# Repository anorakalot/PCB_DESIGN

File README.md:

# PCB_DESIGN
PCB_DESIGN REPOSITORY

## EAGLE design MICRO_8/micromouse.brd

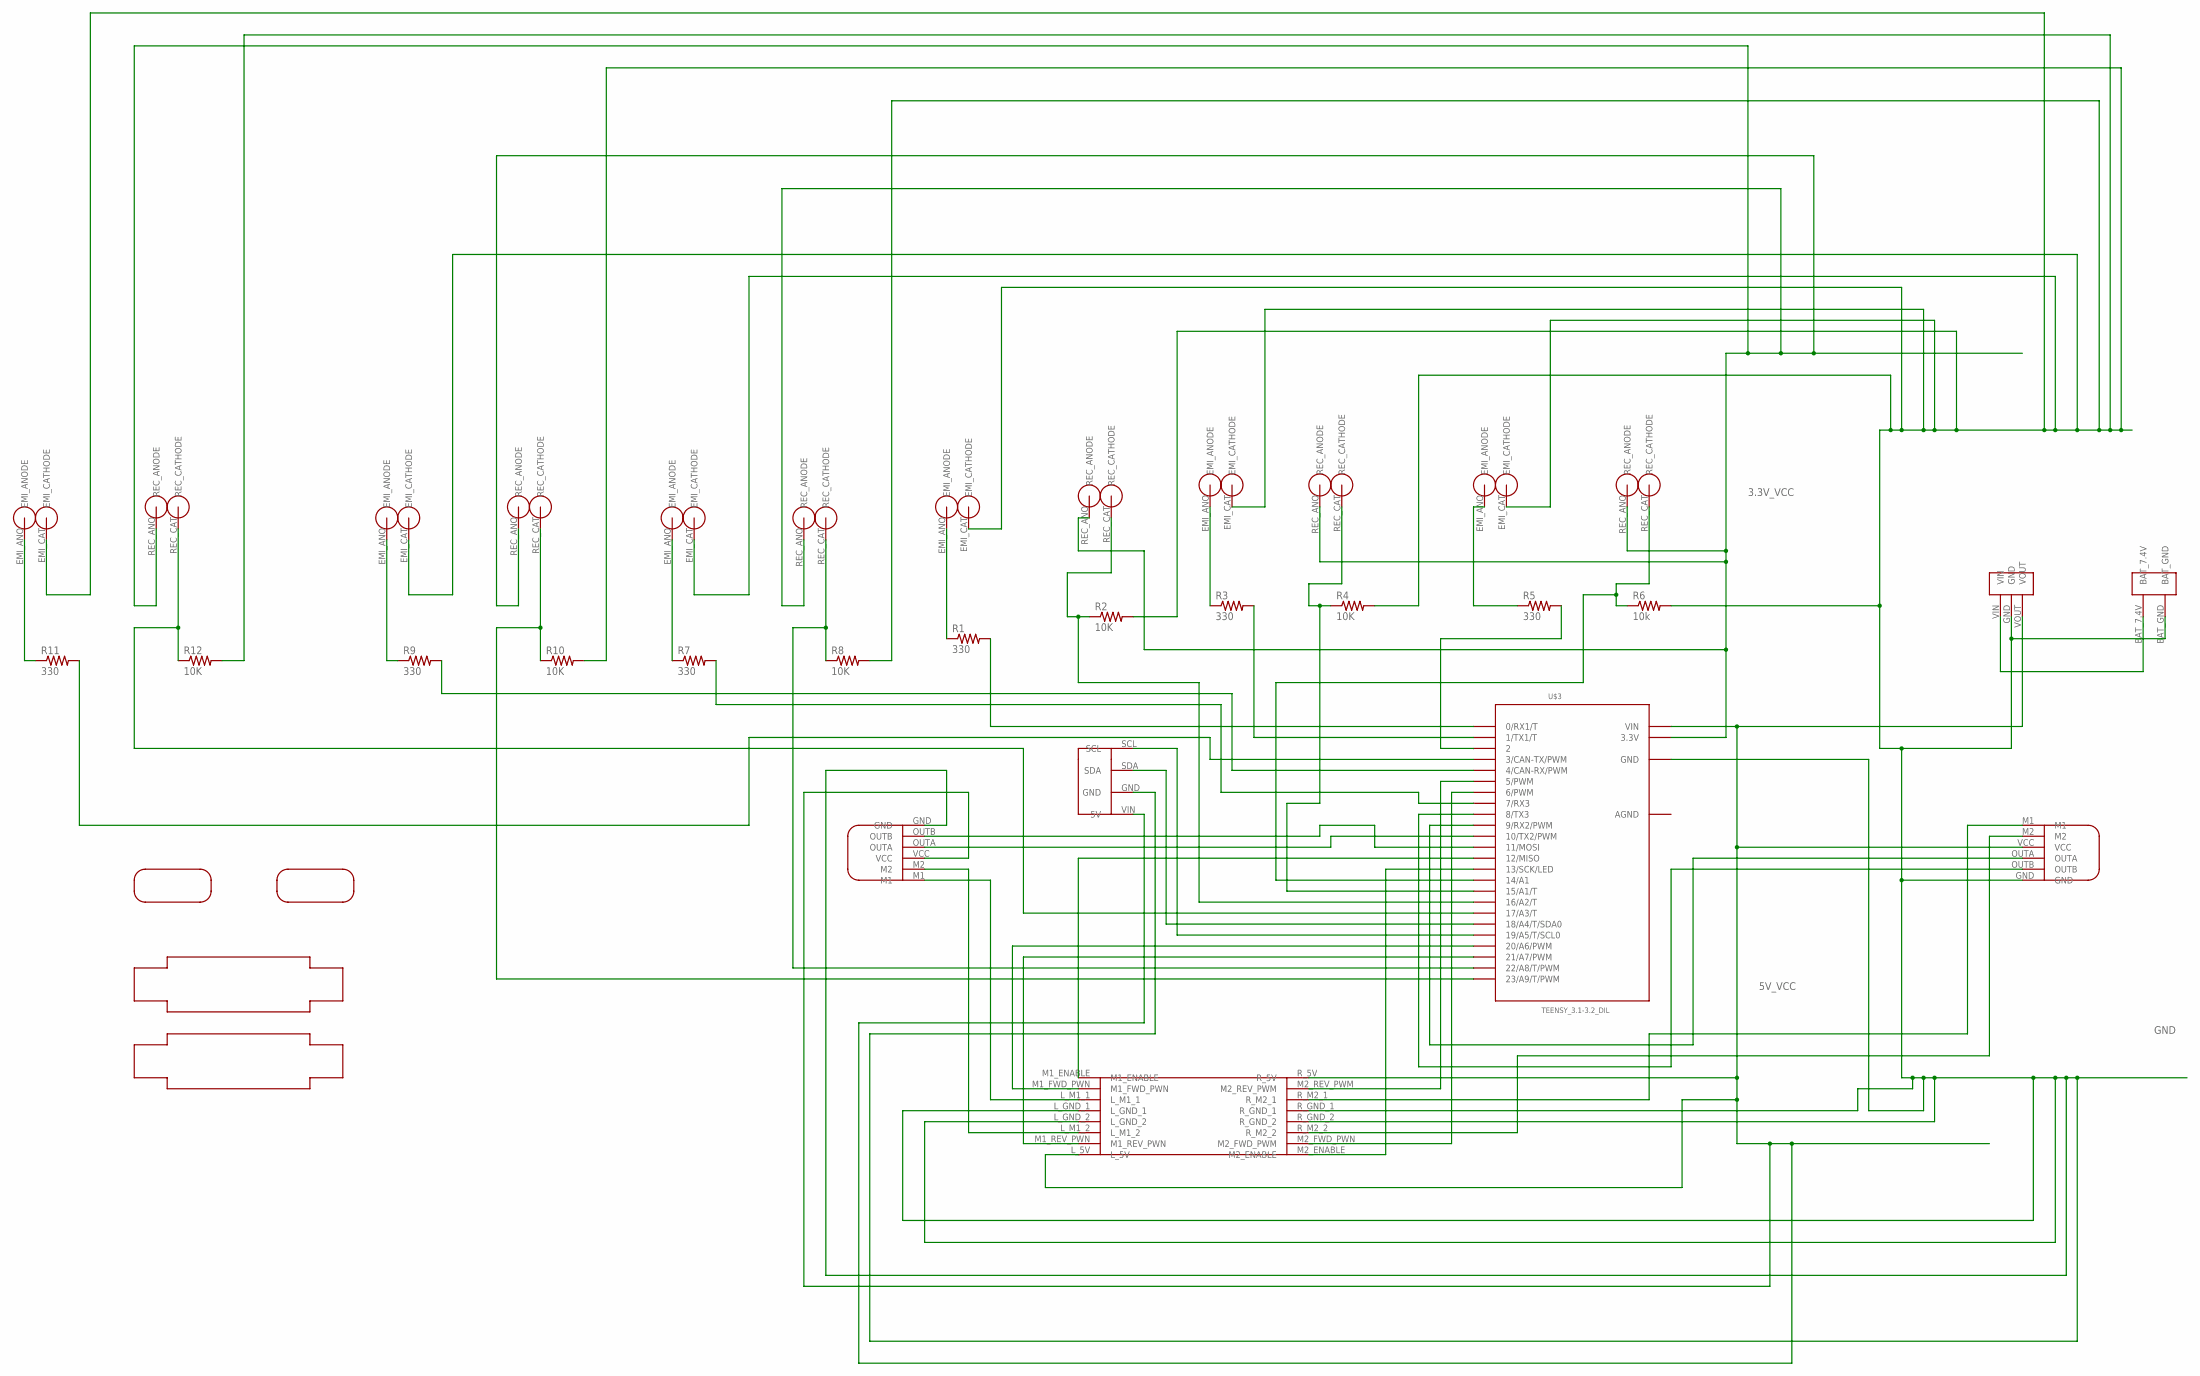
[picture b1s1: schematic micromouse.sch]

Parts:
R1, R3, R5, R7, R9, R11: 330; 0207/10
R2, R4, R8, R10, R12: 10K; 0207/10
R6: 10k; 0207/10
U$1, U$2: MOTOR_ENCODER
U$3: TEENSY_3.1-3.2_DIL; TEENSY_3.0-3.2&LC_DIL
U$4: MOTOR_DRIVER
U$5, U$8, U$12, U$15, U$17, U$23: IR_RECIEVER
U$6, U$7, U$9, U$14, U$16, U$22: IR_EMITTER
U$10: VOLTAGE_REGULATOR
U$11: BATTERY_INPUT
U$13: IMU
U$18, U$19: MOTOR_BRACKET
U$20, U$21: BALL_CASTER

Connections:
3.3V_VCC: U$3.3.3V, U$5.REC_ANO (REC_ANODE), U$8.REC_ANO (REC_ANODE), U$12.REC_ANO (REC_ANODE), U$15.REC_ANO (REC_ANODE), U$17.REC_ANO (REC_ANODE), U$23.REC_ANO (REC_ANODE)
5V_VCC: U$1.VCC, U$2.VCC, U$3.VIN, U$4.L_5V, U$4.R_5V, U$10.VOUT, U$13.VIN (5V)
AGND: U$3.AGND
GND: R2.2, R4.2, R6.2, R8.2, R10.2, R12.2, U$1.GND, U$2.GND, U$3.GND, U$4.L_GND_1, U$4.L_GND_2, U$4.R_GND_1, U$4.R_GND_2, U$6.EMI_CAT (EMI_CATHODE), U$7.EMI_CAT (EMI_CATHODE), U$9.EMI_CAT (EMI_CATHODE), U$10.GND, U$11.BAT_GND, U$13.GND, U$14.EMI_CAT (EMI_CATHODE), U$16.EMI_CAT (EMI_CATHODE), U$22.EMI_CAT (EMI_CATHODE)
M1_FWD_PWM: U$3.20/A6 (20/A6/PWM), U$4.M1_FWD_PWN
M1_L: U$1.M1, U$4.L_M1_1
M1_R: U$2.M1, U$4.R_M2_1
M1_REV_PWM: U$3.21/A7 (21/A7/PWM), U$4.M1_REV_PWN
M2_ENABLE: U$3.13 (13/SCK/LED), U$4.M2_ENABLE
M2_FWD_PWM: U$3.6 (6/PWM), U$4.M2_FWD_PWN (M2_FWD_PWM)
M2_L: U$1.M2, U$4.L_M1_2
M2_R: U$2.M2, U$4.R_M2_2
unnamed: U$10.VIN, U$11.BAT_7.4V
unnamed: U$3.19/A5 (19/A5/T/SCL0), U$13.SCL
unnamed: U$3.18/A4 (18/A4/T/SDA0), U$13.SDA
unnamed: U$3.12 (12/MISO), U$4.M1_ENABLE
unnamed: U$3.5 (5/PWM), U$4.M2_REV_PWM
unnamed: R7.2, U$3.3 (3/CAN-TX/PWM)
unnamed: R7.1, U$14.EMI_ANO (EMI_ANODE)
unnamed: R8.1, U$3.22/A8 (22/A8/T/PWM), U$15.REC_CAT (REC_CATHODE)
unnamed: R9.2, U$3.4 (4/CAN-RX/PWM)
unnamed: R9.1, U$16.EMI_ANO (EMI_ANODE)
unnamed: R11.2, U$3.7 (7/RX3)
unnamed: R10.1, U$3.23/A9 (23/A9/T/PWM), U$17.REC_CAT (REC_CATHODE)
unnamed: R11.1, U$22.EMI_ANO (EMI_ANODE)
unnamed: R12.1, U$3.17/A3 (17/A3/T), U$23.REC_CAT (REC_CATHODE)
unnamed: R1.2, U$3.0 (0/RX1/T)
unnamed: R1.1, U$9.EMI_ANO (EMI_ANODE)
unnamed: R6.1, U$3.14/A0 (14/A1), U$8.REC_CAT (REC_CATHODE)
unnamed: R3.2, U$3.1 (1/TX1/T)
unnamed: R3.1, U$6.EMI_ANO (EMI_ANODE)
unnamed: R4.1, U$3.15/A1 (15/A1/T), U$12.REC_CAT (REC_CATHODE)
unnamed: R5.2, U$3.2
unnamed: R5.1, U$7.EMI_ANO (EMI_ANODE)
unnamed: R2.1, U$3.16/A2 (16/A2/T), U$5.REC_CAT (REC_CATHODE)
OUTA_L: U$1.OUTA, U$3.10 (10/TX2/PWM)
OUTA_R: U$2.OUTA, U$3.9 (9/RX2/PWM)
OUTB_L: U$1.OUTB, U$3.11 (11/MOSI)
OUTB_R: U$2.OUTB, U$3.8 (8/TX3)

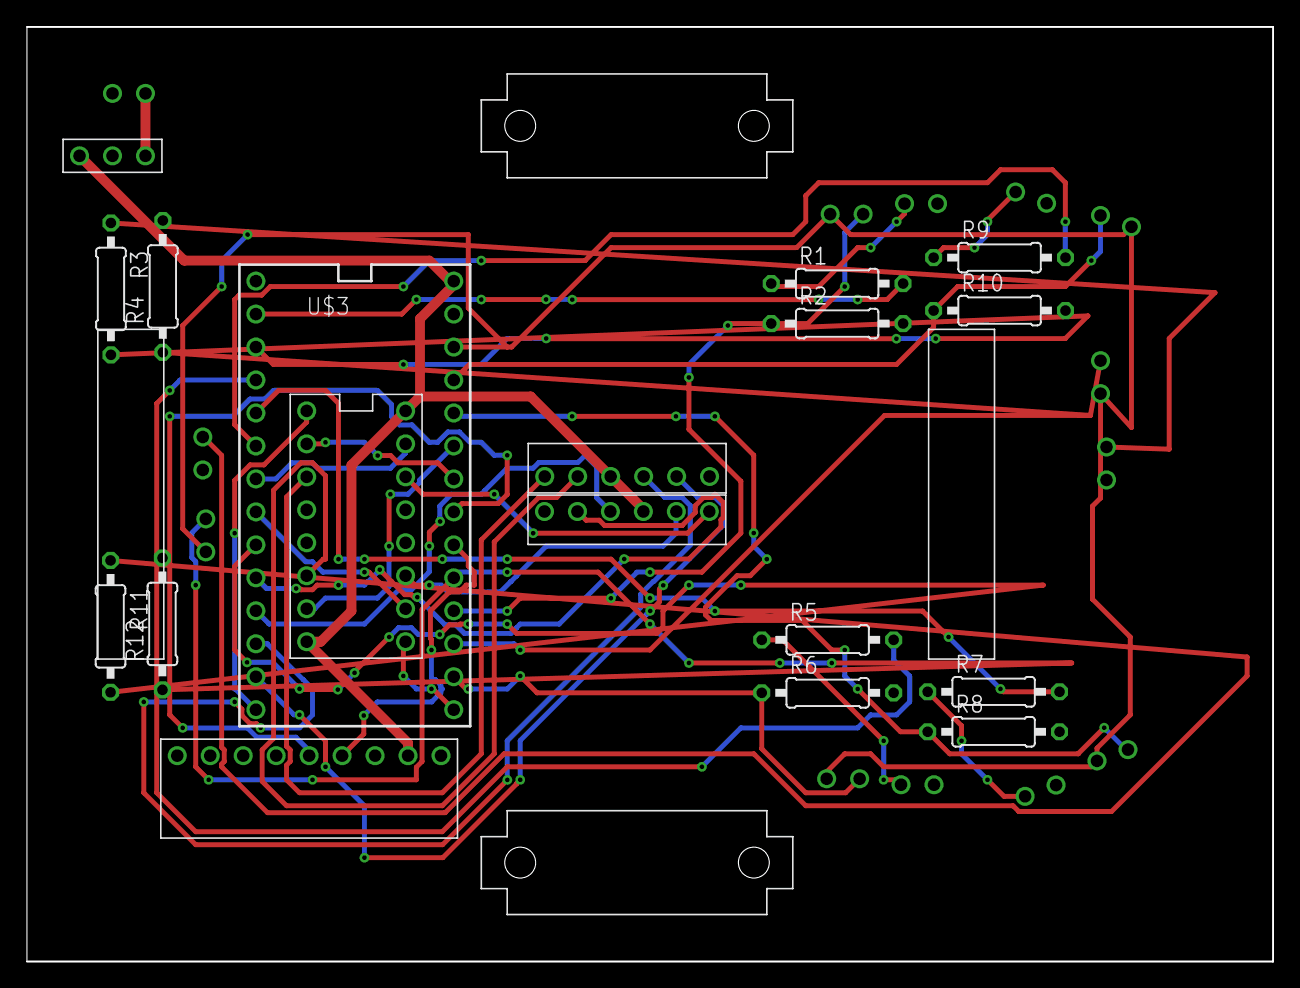
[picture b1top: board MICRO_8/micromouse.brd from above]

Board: 2 copper layers, 96.0 x 72.0 mm, 35 parts (0 on the bottom side), 38 nets.

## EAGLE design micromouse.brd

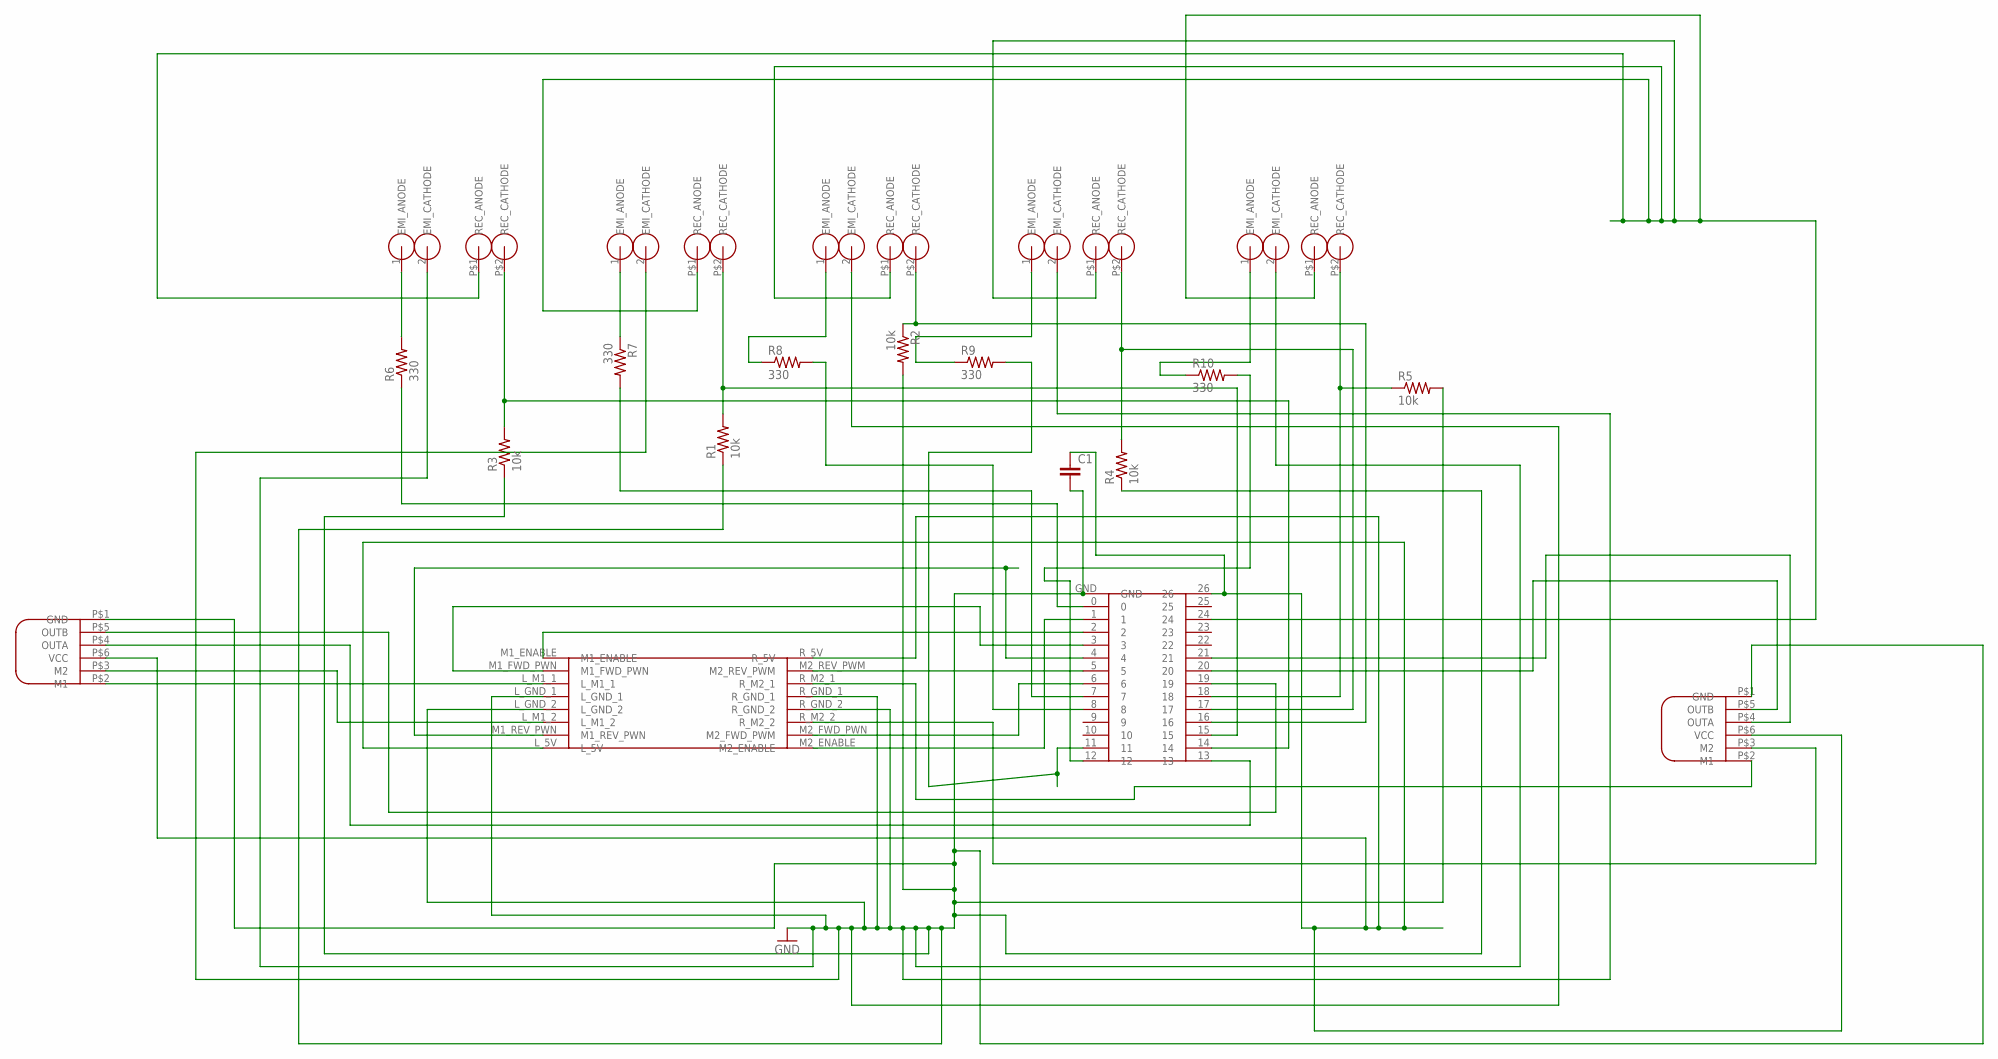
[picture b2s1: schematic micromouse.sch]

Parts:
C1: C2,5-3; C2.5-3
R1, R2, R3, R4, R5: 10k; 0204/5
R6, R7, R8, R9, R10: 330; 0204/5
U$1: TEENSY3.2
U$2: MOTOR_DRIVER
U$3, U$4, U$5, U$6, U$7: IR_RECIEVER
U$8, U$9, U$10, U$11, U$12: IR_EMITTER
U$13, U$14: MOTOR_ENCODER

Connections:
GND: C1.2, R1.1, R2.2, R3.1, R4.1, R5.2, U$1.GND, U$2.L_GND_1, U$2.L_GND_2, U$2.R_GND_1, U$2.R_GND_2, U$8.2 (EMI_CATHODE), U$9.2 (EMI_CATHODE), U$10.2 (EMI_CATHODE), U$11.2 (EMI_CATHODE), U$12.2 (EMI_CATHODE), U$13.P$1 (GND), U$14.P$1 (GND)
unnamed: U$1.2, U$2.M1_ENABLE
unnamed: U$1.3, U$2.M1_FWD_PWN
unnamed: U$2.L_M1_2, U$13.P$3 (M2)
unnamed: U$1.1, U$2.M2_ENABLE
unnamed: U$1.5, U$2.M2_REV_PWM
unnamed: U$2.R_M2_2, U$14.P$3 (M2)
unnamed: U$1.6, U$2.M2_FWD_PWN (M2_FWD_PWM)
unnamed: U$1.4, U$2.M1_REV_PWN
unnamed: R6.2, U$8.1 (EMI_ANODE)
unnamed: R6.1, U$1.0
unnamed: R7.1, U$9.1 (EMI_ANODE)
unnamed: R7.2, U$1.7
unnamed: R8.1, U$10.1 (EMI_ANODE)
unnamed: R8.2, U$1.8
unnamed: R9.1, U$11.1 (EMI_ANODE)
unnamed: R9.2, U$1.11
unnamed: R10.1, U$12.1 (EMI_ANODE)
unnamed: R10.2, U$1.12
unnamed: R1.2, U$1.15, U$4.P$2 (REC_CATHODE)
unnamed: R2.1, U$1.16, U$5.P$2 (REC_CATHODE)
unnamed: R4.2, U$1.17, U$6.P$2 (REC_CATHODE)
unnamed: R5.1, U$1.18, U$7.P$2 (REC_CATHODE)
unnamed: R3.2, U$1.14, U$3.P$2 (REC_CATHODE)
unnamed: U$2.L_M1_1, U$13.P$2 (M1)
unnamed: U$1.20, U$14.P$5 (OUTB)
unnamed: U$1.13, U$13.P$4 (OUTA)
unnamed: U$1.21, U$14.P$4 (OUTA)
unnamed: U$1.19, U$13.P$5 (OUTB)
unnamed: C1.1, U$1.26, U$2.L_5V, U$2.R_5V, U$13.P$6 (VCC), U$14.P$6 (VCC)
unnamed: U$2.R_M2_1, U$14.P$2 (M1)
unnamed: U$1.24, U$3.P$1 (REC_ANODE), U$4.P$1 (REC_ANODE), U$5.P$1 (REC_ANODE), U$6.P$1 (REC_ANODE), U$7.P$1 (REC_ANODE)

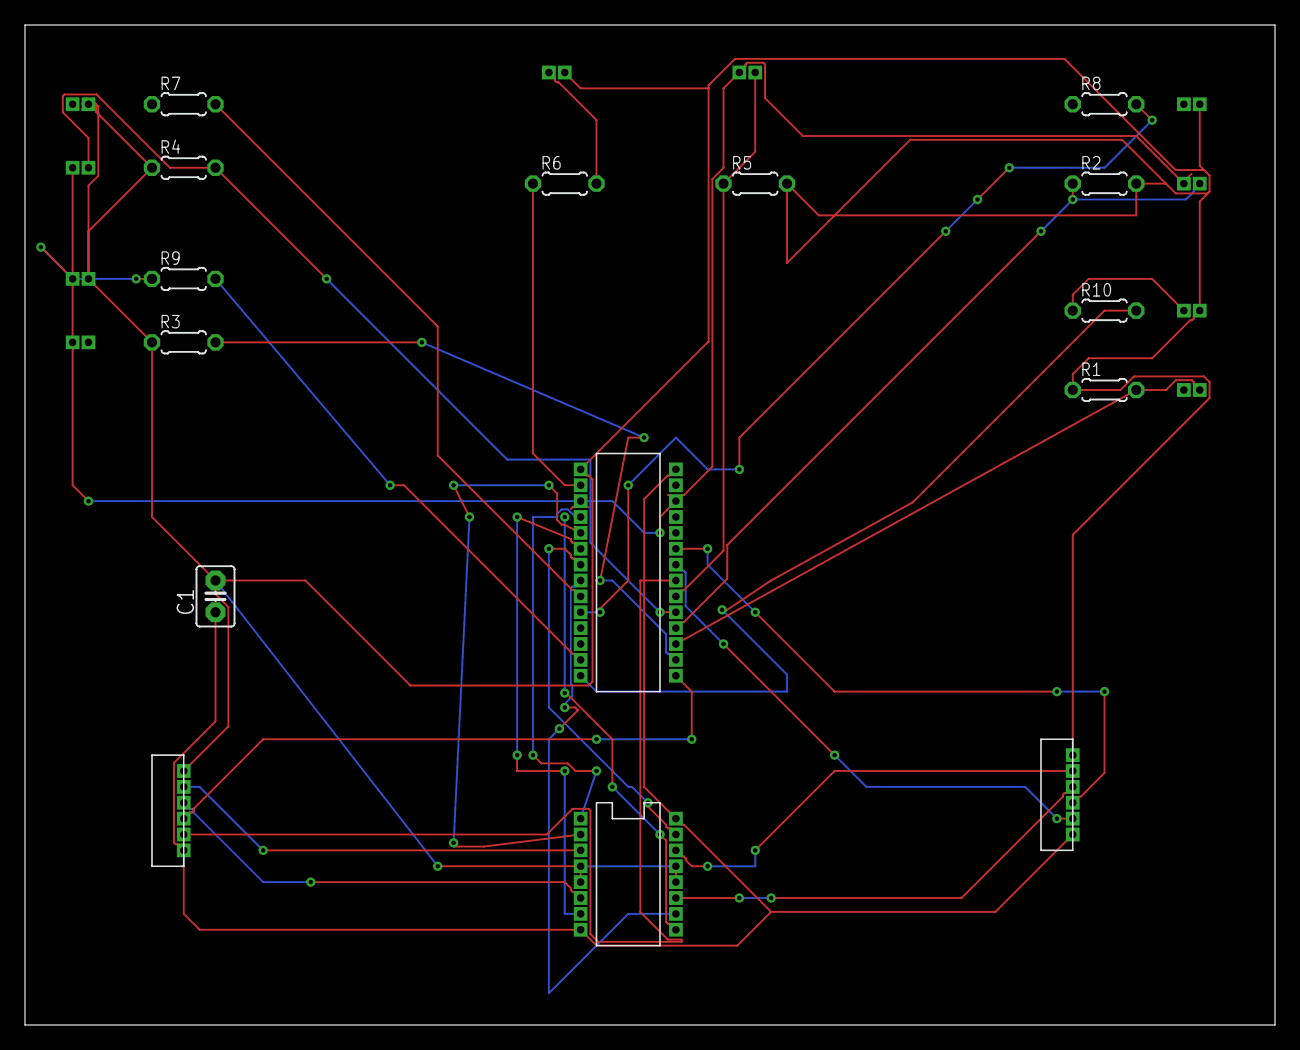
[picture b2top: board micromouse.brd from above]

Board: 2 copper layers, 100.0 x 80.0 mm, 25 parts (0 on the bottom side), 32 nets.

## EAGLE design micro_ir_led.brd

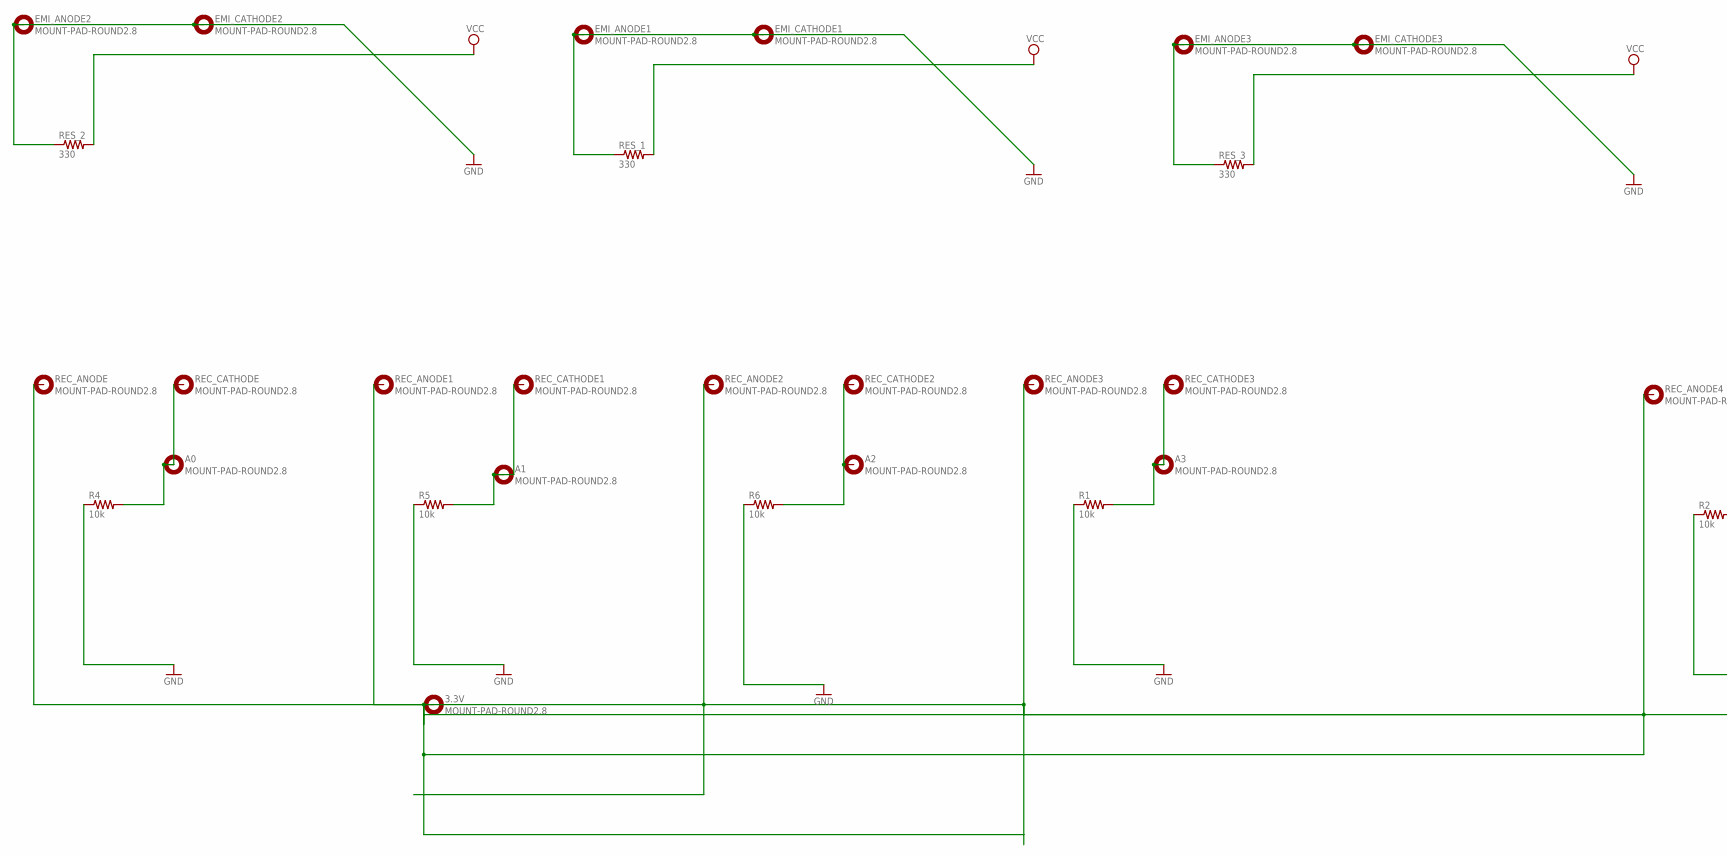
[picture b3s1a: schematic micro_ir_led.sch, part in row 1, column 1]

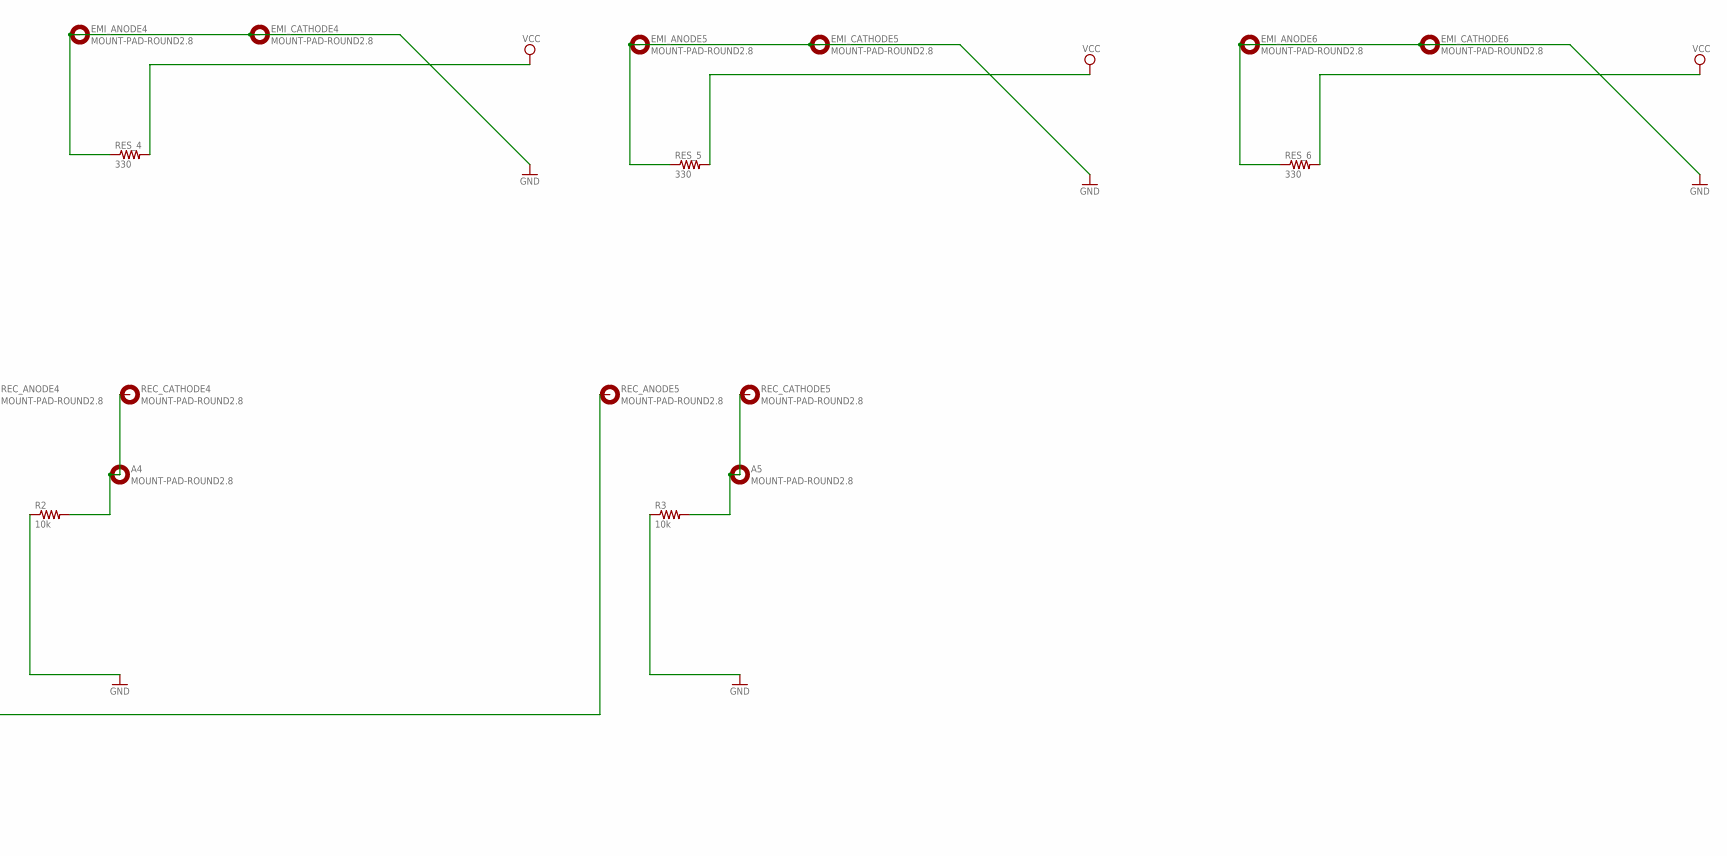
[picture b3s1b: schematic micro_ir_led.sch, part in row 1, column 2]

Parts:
3.3V: MOUNT-PAD-ROUND2.8; 2,8-PAD
A0, A1, A2, A3, A4, A5: MOUNT-PAD-ROUND2.8; 2,8-PAD
EMI_ANODE1, EMI_ANODE2, EMI_ANODE3, EMI_ANODE4, EMI_ANODE5, EMI_ANODE6: MOUNT-PAD-ROUND2.8; 2,8-PAD
EMI_CATHODE1, EMI_CATHODE2, EMI_CATHODE3, EMI_CATHODE4, EMI_CATHODE5, EMI_CATHODE6: MOUNT-PAD-ROUND2.8; 2,8-PAD
R1, R2, R3, R4, R5, R6: 10k; 0204V
REC_ANODE, REC_ANODE1, REC_ANODE2, REC_ANODE3, REC_ANODE4, REC_ANODE5: MOUNT-PAD-ROUND2.8; 2,8-PAD
REC_CATHODE, REC_CATHODE1, REC_CATHODE2, REC_CATHODE3, REC_CATHODE4, REC_CATHODE5: MOUNT-PAD-ROUND2.8; 2,8-PAD
RES_1, RES_2, RES_3, RES_4, RES_5, RES_6: 330; 0204V

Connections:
GND: EMI_ANODE1.B2,8, EMI_ANODE2.B2,8, EMI_ANODE3.B2,8, EMI_ANODE4.B2,8, EMI_ANODE5.B2,8, EMI_ANODE6.B2,8, EMI_CATHODE1.B2,8, EMI_CATHODE2.B2,8, EMI_CATHODE3.B2,8, EMI_CATHODE4.B2,8, EMI_CATHODE5.B2,8, EMI_CATHODE6.B2,8, R1.1, R2.1, R3.1, R4.1, R5.1, R6.1, RES_1.1, RES_2.1, RES_3.1, RES_4.1, RES_5.1, RES_6.1
unnamed: 3.3V.B2,8, REC_ANODE.B2,8, REC_ANODE1.B2,8, REC_ANODE2.B2,8, REC_ANODE3.B2,8, REC_ANODE4.B2,8
unnamed: A0.B2,8, R4.2, REC_CATHODE.B2,8
unnamed: A1.B2,8, R5.2, REC_CATHODE1.B2,8
unnamed: A2.B2,8, R6.2, REC_CATHODE2.B2,8
unnamed: A3.B2,8, R1.2, REC_CATHODE3.B2,8
unnamed: A4.B2,8, R2.2, REC_CATHODE4.B2,8
unnamed: A5.B2,8, R3.2, REC_CATHODE5.B2,8
VCC: RES_1.2, RES_2.2, RES_3.2, RES_4.2, RES_5.2, RES_6.2

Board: 2 copper layers, 43 parts (0 on the bottom side), 9 nets, no tracks yet.

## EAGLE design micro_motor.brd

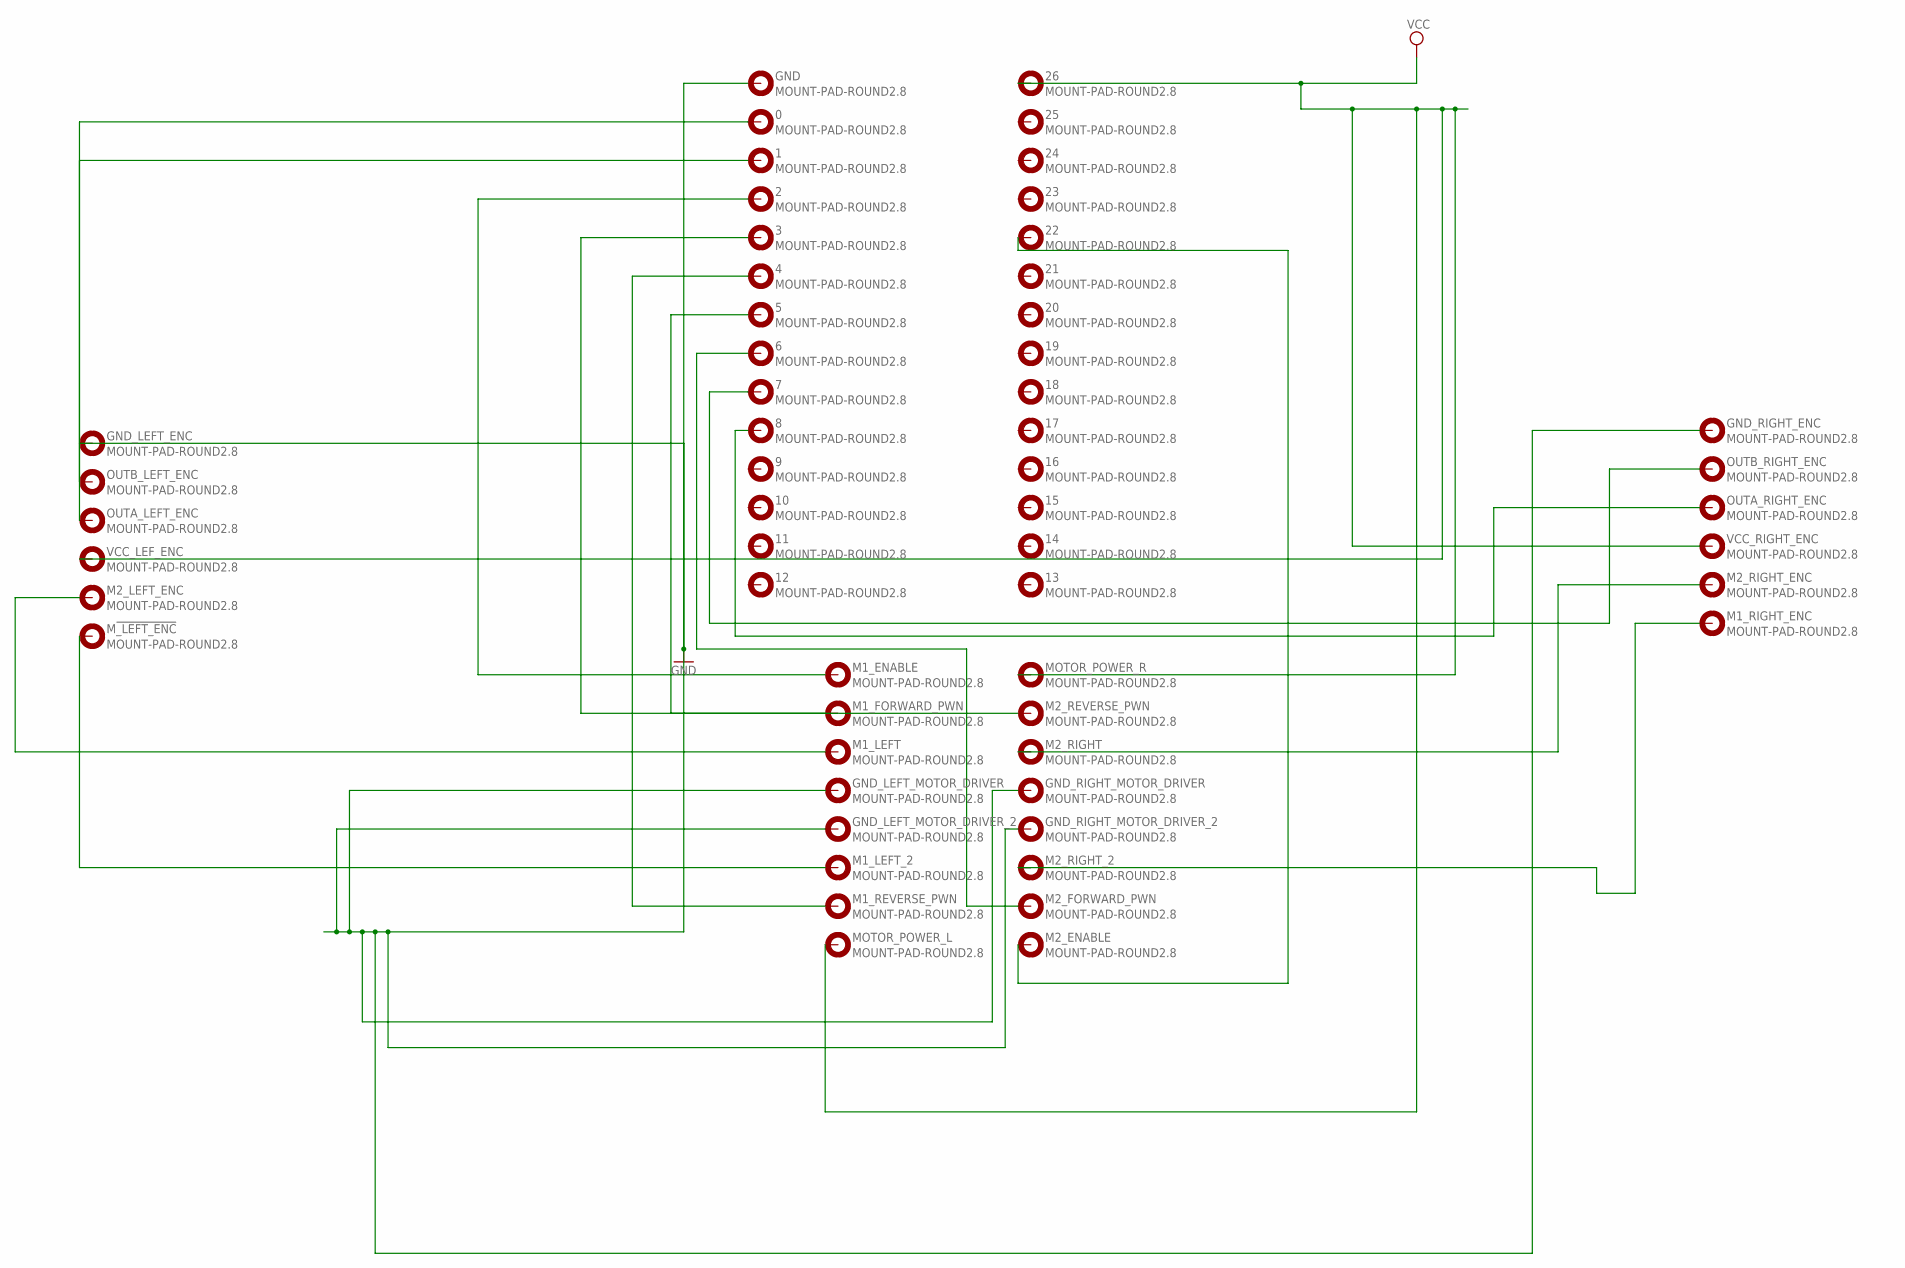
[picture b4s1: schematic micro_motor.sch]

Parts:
0, 1, 2, 3, 4, 5, 6, 7, 8, 9, 10, 11, 12, 13, 14, 15, 16, 17, 18, 19, 20, 21, 22, 23, 24, 25, 26: MOUNT-PAD-ROUND2.8; 2,8-PAD
GND: MOUNT-PAD-ROUND2.8; 2,8-PAD
GND_LEFT_ENC: MOUNT-PAD-ROUND2.8; 2,8-PAD
GND_LEFT_MOTOR_DRIVER: MOUNT-PAD-ROUND2.8; 2,8-PAD
GND_LEFT_MOTOR_DRIVER_2: MOUNT-PAD-ROUND2.8; 2,8-PAD
GND_RIGHT_ENC: MOUNT-PAD-ROUND2.8; 2,8-PAD
GND_RIGHT_MOTOR_DRIVER: MOUNT-PAD-ROUND2.8; 2,8-PAD
GND_RIGHT_MOTOR_DRIVER_2: MOUNT-PAD-ROUND2.8; 2,8-PAD
M1_ENABLE, M1_FORWARD_PWN, M1_LEFT, M1_LEFT_2, M1_REVERSE_PWN, M1_RIGHT_ENC, M2_ENABLE, M2_FORWARD_PWN, M2_LEFT_ENC, M2_REVERSE_PWN, M2_RIGHT, M2_RIGHT_2, M2_RIGHT_ENC: MOUNT-PAD-ROUND2.8; 2,8-PAD
M!_LEFT_ENC: MOUNT-PAD-ROUND2.8; 2,8-PAD
MOTOR_POWER_L: MOUNT-PAD-ROUND2.8; 2,8-PAD
MOTOR_POWER_R: MOUNT-PAD-ROUND2.8; 2,8-PAD
OUTA_LEFT_ENC: MOUNT-PAD-ROUND2.8; 2,8-PAD
OUTA_RIGHT_ENC: MOUNT-PAD-ROUND2.8; 2,8-PAD
OUTB_LEFT_ENC: MOUNT-PAD-ROUND2.8; 2,8-PAD
OUTB_RIGHT_ENC: MOUNT-PAD-ROUND2.8; 2,8-PAD
VCC_LEF_ENC: MOUNT-PAD-ROUND2.8; 2,8-PAD
VCC_RIGHT_ENC: MOUNT-PAD-ROUND2.8; 2,8-PAD

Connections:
GND: GND.B2,8, GND_LEFT_ENC.B2,8, GND_LEFT_MOTOR_DRIVER.B2,8, GND_LEFT_MOTOR_DRIVER_2.B2,8, GND_RIGHT_ENC.B2,8, GND_RIGHT_MOTOR_DRIVER.B2,8, GND_RIGHT_MOTOR_DRIVER_2.B2,8
unnamed: 0.B2,8, OUTB_LEFT_ENC.B2,8
unnamed: 1.B2,8, OUTA_LEFT_ENC.B2,8
unnamed: M1_LEFT.B2,8, M2_LEFT_ENC.B2,8
unnamed: 3.B2,8, M1_FORWARD_PWN.B2,8
unnamed: 4.B2,8, M1_REVERSE_PWN.B2,8
unnamed: 2.B2,8, M1_ENABLE.B2,8
unnamed: 8.B2,8, OUTA_RIGHT_ENC.B2,8
unnamed: M2_RIGHT.B2,8, M2_RIGHT_ENC.B2,8
unnamed: 7.B2,8, OUTB_RIGHT_ENC.B2,8
unnamed: M1_RIGHT_ENC.B2,8, M2_RIGHT_2.B2,8
unnamed: M1_LEFT_2.B2,8, M!_LEFT_ENC.B2,8
unnamed: 5.B2,8, M2_REVERSE_PWN.B2,8
unnamed: 22.B2,8, M2_ENABLE.B2,8
unnamed: 6.B2,8, M2_FORWARD_PWN.B2,8
VCC: 26.B2,8, MOTOR_POWER_L.B2,8, MOTOR_POWER_R.B2,8, VCC_LEF_ENC.B2,8, VCC_RIGHT_ENC.B2,8

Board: 2 copper layers, 56 parts (0 on the bottom side), 16 nets, no tracks yet.

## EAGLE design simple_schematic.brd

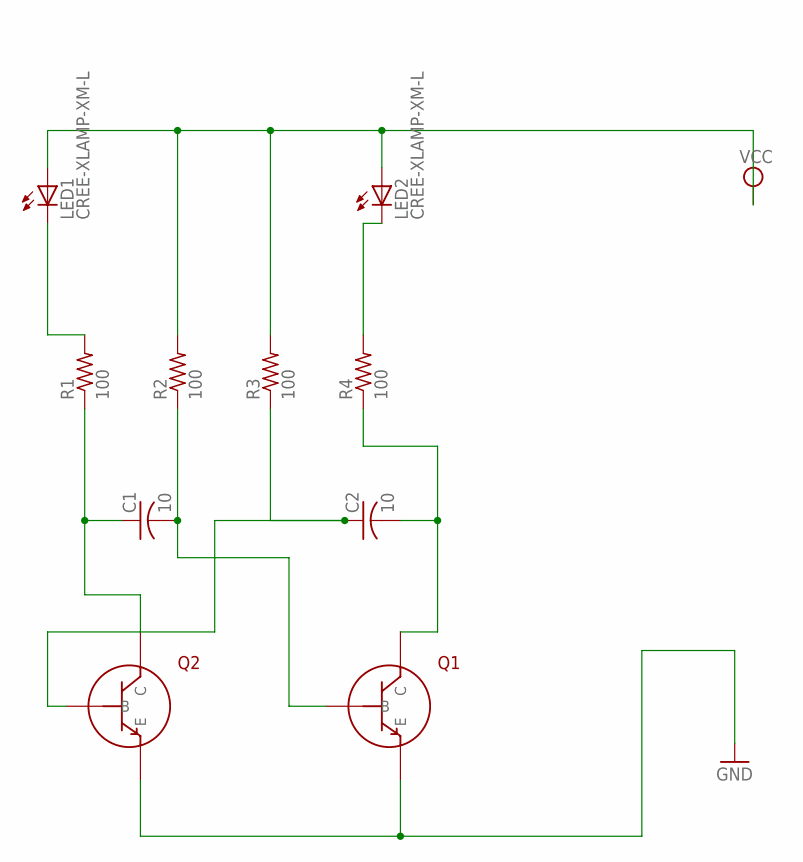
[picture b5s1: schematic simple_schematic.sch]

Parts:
C1, C2: 10; C025-024X044
LED1, LED2: CREE-XLAMP-XM-L
R1, R2, R3, R4: 100; 0204V

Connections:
unnamed: LED2.C, LED2.C@1 (C), R4.2
unnamed: LED1.C, LED1.C@1 (C), R1.2
unnamed: C1.1, R1.1
unnamed: C1.2, R2.1
unnamed: C2.1, R3.1
unnamed: C2.2, R4.1
VCC: LED1.A, LED1.A@1 (A), LED2.A, LED2.A@1 (A), R2.2, R3.2

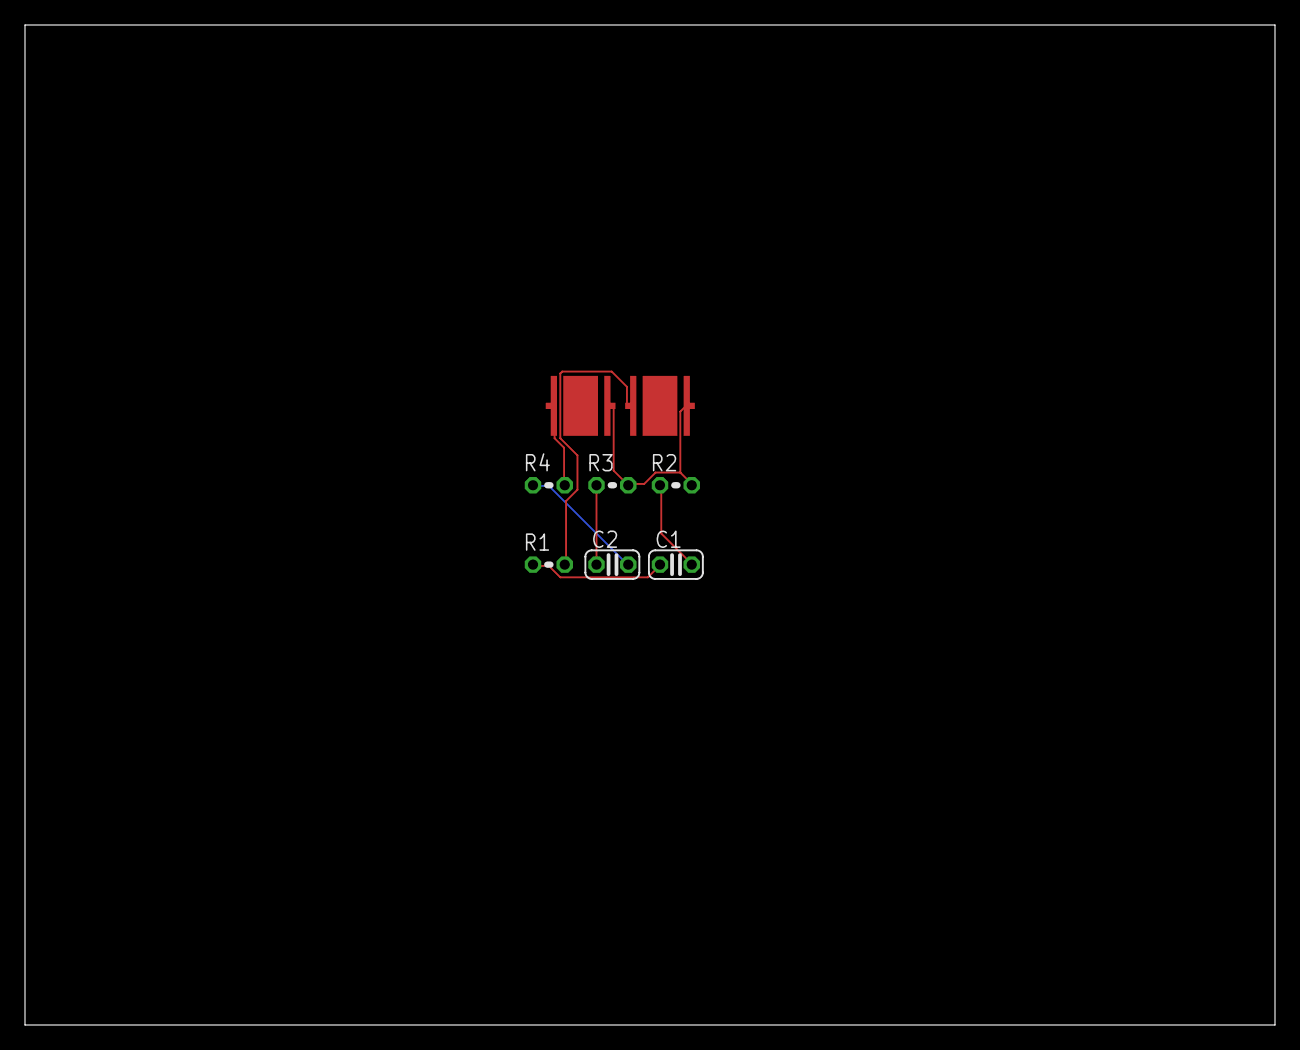
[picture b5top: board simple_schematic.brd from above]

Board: 2 copper layers, 100.0 x 80.0 mm, 8 parts (0 on the bottom side), 7 nets.

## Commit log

2018-06-21 Create LICENSE
2019-02-24 added imu component
2019-02-25 Fixed wrong connections for encoder
2019-02-25 added 2 extra ir pairs
2019-02-26 added some traces
2019-02-27 put in more traces
    fall back to this if putting all traces on a single layer does not work
2019-02-28 make 5v and 3.3v traces 12 mil and just dont worry about gound plane
2019-02-28 only traces left are IMU traces after this check then turn in
2019-03-01 finished all traces drc run with no errors
2019-03-01 made the side leds 45 degree angle
2019-03-01 final pcb design for this year unless somethings wrong
2019-03-01 final changes for pcb for first competitions
2019-03-16 added ground plane and a capacitor use this if current PCB doesn't work
2019-03-23 added gnd plane/fixed dimensions
2019-03-23 thru hole for use with motor brackets
2019-05-11 new mouse
2019-05-11 power and gnd planes
2019-05-12 added motor_bracket lbr. need to fix dimension so motor bracket is in mm and board is in mil
2019-05-13 changed emitter library to make them more consistent
2019-05-13 45 degrees placed
2019-05-13 45 placed again but this is more precise
2019-05-14 all the traces on top layer alone next will include bottom layer for traces
2019-05-14 all routes are traced
2019-05-14 made more space for motors
2019-05-14 made more space for ir's so they can fit onto the board
2019-05-20 had there not be plane for the motor_brackets so it's easier to drill them
2019-05-20 added more space in between led's
2019-06-15 put in ir on the back for floodfill , added new ground and vcc plane to stay out of drill hole range to make it safer
2019-07-19 made 45 degrees sensors into 20 degree sensors
    so it stays in current cell for ir control. Put irs back so they fit on the board and won't stick out (need to double check). replaced middle resistors for more space. replaced motor brackets so they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
2019-07-19 cut out part near the motor so the motor can be closer in and be less likely to get stuck
2019-07-20 cut out parts on all four sides of mouse so it can manuever better. Last thing is when led's come in is to double check measurements and correct them in pcb so they fit onto the board
2019-07-30 put in led's into proper spacing so they fit onto the board. This is last commit before I start tracing so come back to this is somethings was wrong beforehand
2019-10-16 micro_6 is made mouse that works good except for wire placement, micro_7 has new placement of motors in the middle for better turning
2019-10-17 added back place for ball caster
2019-10-26 traced all of the connections
2021-06-21 made an OV7670 Camera Library for PCB DESIGN
2021-06-28 started_work_on ov7670 circ using info from online but having to change it due to using a teensy board
2021-12-25 made encoder 25D library for bigger gearmotor used in Senior Design
2021-12-25 second version of senior design base mapping robot
